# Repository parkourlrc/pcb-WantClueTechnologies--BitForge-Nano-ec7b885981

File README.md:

# 🪙 Open Source Bitcoin Miner PCB – CERN OHL 2 - S Licensed

This project presents a fully open-source Bitcoin mining hardware platform, designed for transparency, modularity, and extensibility. Built around the BM1370 ASICs and powered by an ESP32-S3 microcontroller, this board offers a compact yet powerful solution for enthusiasts and developers interested in cryptocurrency mining hardware.

Released under the **CERN OHL 2 S**, all design files, firmware, and documentation are freely available for use, modification, and redistribution.

---

## 📌 Key Features

- **Open Source Hardware & Firmware** – CERN-OHL-S licensed
- **Dual BM1370 ASICs** for parallel mining
- **ESP32-S3** as the central controller
- **Precision power monitoring** via INA260
- **Multi-stage voltage regulation** from 12 V down to 0.8 V
- **UART communication** with level shifting
- **Temperature monitoring & fan control** per ASIC
- **USB-C interface** for firmware upload and updates
- **Status LEDs** for visual feedback
- **Modular I2C architecture** with multiplexer support

---

## 🔧 Technical Overview

### Power Architecture

The board is powered via a **12 V barrel jack**, with a recommended power supply of **at least 70 W** to ensure stable operation under full load. Power distribution is carefully managed through multiple buck converters:

- **TPS546A24 Buck Converter**: Converts 12 V to **1.2 V**, configurable via **SMBus/I2C**
- **12 V → 5 V Buck Converter**
- **5 V → 3.3 V Buck Converter**
- From 3.3 V, two reference voltages (**1.2 V and 0.8 V**) are derived for the ASICs

A **Texas Instruments INA260** is used to monitor the total current and voltage, providing accurate power consumption data for the entire board and its peripherals.

---

### ASICs & Communication

The core mining functionality is handled by **two BM1370 ASICs**, connected in parallel and powered by the regulated 1.2 V supply. These chips communicate via **UART**, with signal levels adjusted using a **SN74AVC level shifter** to ensure compatibility between the ESP32-S3 and the ASICs.

Each ASIC requires two reference voltages (1.2 V and 0.8 V), which are derived from the 3.3 V rail using dedicated regulators.

---

### Thermal Management & Fan Control

Each BM1370 ASIC includes an internal die temperature sensor, which is monitored by an **EMC2101** temperature controller. These controllers also support **PWM fan control**, allowing each ASIC to drive a dedicated **12 V cooling fan**.

Since the EMC2101 has a fixed I2C address, a **PCA9544 I2C multiplexer** is used to switch between the two devices, enabling independent monitoring and control.

---

### Control & Interfaces

At the heart of the board is an **ESP32-S3**, which runs the firmware responsible for:

- ASIC initialization and control
- Power and temperature monitoring
- Fan speed regulation
- Communication via UART and I2C
- Status indication via **two onboard LEDs**

A **USB-C port** is provided for firmware flashing and future updates, making development and deployment straightforward.

---

## 🛠️ Open Source & Licensing

This project is proudly released under the **CERN Open Hardware Licence Version 2 - Strongly Reciprocal (CERN-OHL-S)**. This means:

- You are free to use, study, modify, and distribute the hardware designs
- Any derivative work must also be released under CERN-OHL-S
- If you manufacture or distribute products based on this design, you must provide recipients with access to the complete source files
- Contributions and improvements are welcome!

The CERN-OHL-S is specifically designed for open-source hardware, ensuring that designs remain open and accessible. We believe in open collaboration and transparency, and by releasing this project under CERN-OHL-S, we aim to foster innovation in the hardware mining community and provide a solid foundation for further development.

For the full license text, see the [LICENSE](LICENSE) file.

---

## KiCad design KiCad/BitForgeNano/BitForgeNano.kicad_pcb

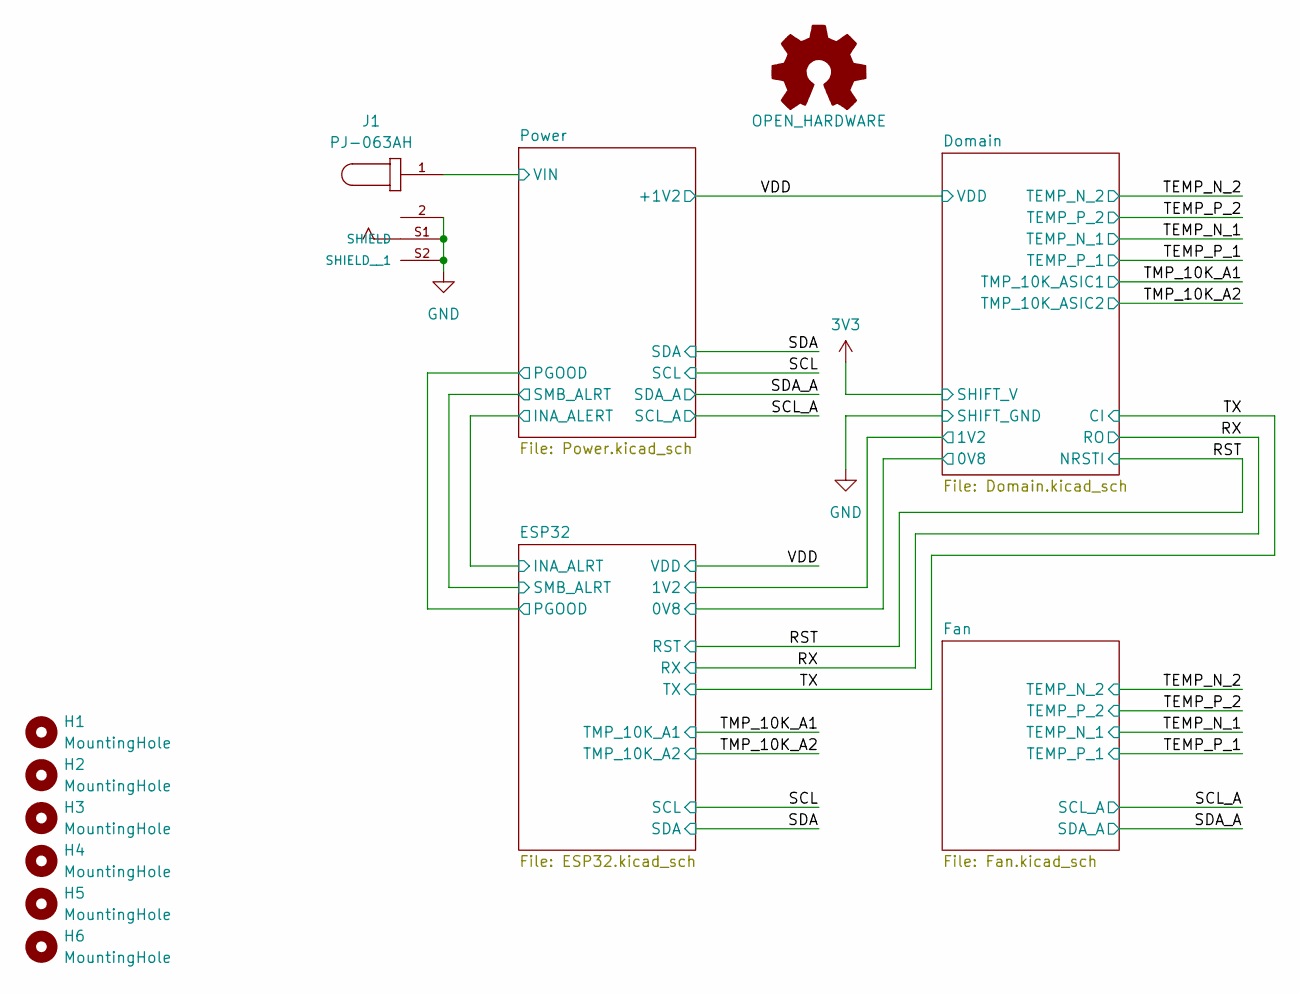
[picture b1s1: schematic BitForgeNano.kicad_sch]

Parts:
H1, H2, H3, H4, H5, H6: MountingHole; MountingHole_3.2mm_M3_ISO14580
J1: PJ-063AH; BarrelJack_CUI_PJ-063AH_Horizontal; PARTREV 1.02
LOGO1: OPEN_HARDWARE; OSHW-Logo_5.7x6mm_SilkScreen

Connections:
/Power/VIN: J1.1; also elsewhere on the board
GND: J1.2, J1.S1 (SHIELD), J1.S2 (SHIELD__1); also elsewhere on the board

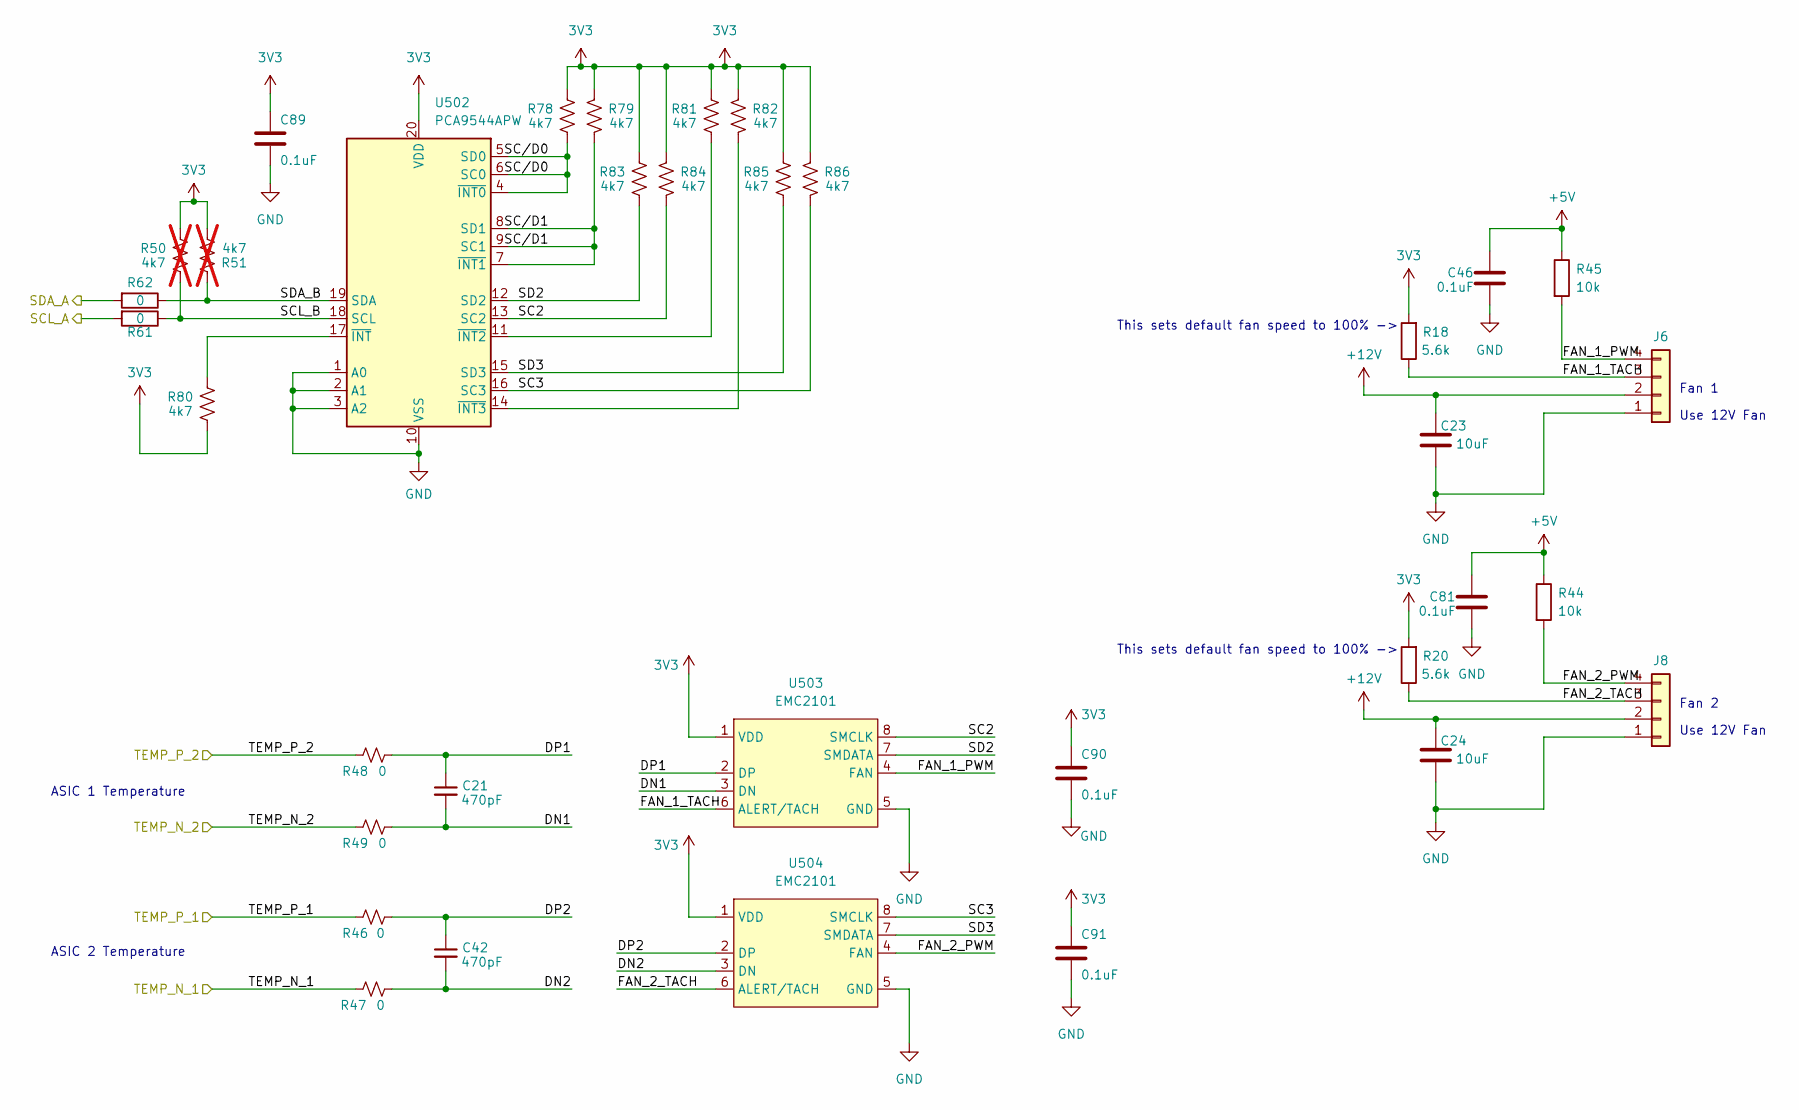
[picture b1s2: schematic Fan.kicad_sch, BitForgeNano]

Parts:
C21, C42: 470pF; C_0402_1005Metric; PARTNO GRM1555C1H471JA01D
C23, C24: 10uF; C_0603_1608Metric
C46, C81: 0.1uF; C_0402_1005Metric; PARTNO KGM05AR71C104KH
C89, C90, C91: 0.1uF; C_0402_1005Metric
J6, J8: Conn_01x04; 470531000; PARTNO 0470531000
R18, R20: 5.6k; R_0402_1005Metric
R44, R45: 10k; R_0402_1005Metric
R46, R47, R48, R49, R61, R62: 0; R_0402_1005Metric; PARTNO RC0402JR-070RL
R50, R51: 4k7; R_0805_2012Metric; not fitted
R78, R79, R80, R81, R82, R83, R84, R85, R86: 4k7; R_0402_1005Metric
U502: PCA9544APW; TSSOP-20_4.4x6.5mm_P0.65mm
U503, U504: EMC2101; TSSOP-8_3x3mm_P0.65mm; PARTNO EMC2101-R-ACZL-TR

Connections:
3V3: C89.1, C90.1, C91.1, R18.2, R20.2, R50.2, R51.1, R78.2, R79.2, R80.1, R81.2, R82.2, R83.2, R84.2, R85.2, R86.2, U502.20 (VDD), U503.1 (VDD), U504.1 (VDD); also elsewhere on the board
+5V: C46.1, C81.1, R44.1, R45.1; also elsewhere on the board
+12V: C23.1, C24.1, J6.2, J8.2; also elsewhere on the board
/Fan/DN1: C21.2, R49.1, U503.3 (DN)
/Fan/DN2: C42.2, R47.1, U504.3 (DN)
/Fan/DP1: C21.1, R48.1, U503.2 (DP)
/Fan/DP2: C42.1, R46.1, U504.2 (DP)
/Fan/FAN_1_PWM: J6.4, R45.2, U503.4 (FAN)
/Fan/FAN_1_TACH: J6.3, R18.1, U503.6 (ALERT/TACH)
/Fan/FAN_2_PWM: J8.4, R44.2, U504.4 (FAN)
/Fan/FAN_2_TACH: J8.3, R20.1, U504.6 (ALERT/TACH)
/Fan/SC2: R84.1, U502.13 (SC2), U503.8 (SMCLK)
/Fan/SC3: R86.1, U502.16 (SC3), U504.8 (SMCLK)
/Fan/SCL_B: R50.1, R61.1, U502.18 (SCL)
/Fan/SC/D0: R78.1, U502.4 (~INT0), U502.5 (SD0), U502.6 (SC0)
/Fan/SC/D1: R79.1, U502.7 (~INT1), U502.8 (SD1), U502.9 (SC1)
/Fan/SD2: R83.1, U502.12 (SD2), U503.7 (SMDATA)
/Fan/SD3: R85.1, U502.15 (SD3), U504.7 (SMDATA)
/Fan/SDA_B: R51.2, R62.1, U502.19 (SDA)
/SCL_A: R61.2; also elsewhere on the board
/SDA_A: R62.2; also elsewhere on the board
/TEMP_N_1: R47.2; also elsewhere on the board
/TEMP_N_2: R49.2; also elsewhere on the board
/TEMP_P_1: R46.2; also elsewhere on the board
/TEMP_P_2: R48.2; also elsewhere on the board
GND: C23.2, C24.2, C46.2, C81.2, C89.2, C90.2, C91.2, J6.1, J8.1, U502.1 (A0), U502.2 (A1), U502.3 (A2), U502.10 (VSS), U503.5 (GND), U504.5 (GND); also elsewhere on the board
unnamed: R81.1, U502.11 (~INT2)
unnamed: R82.1, U502.14 (~INT3)
unnamed: R80.2, U502.17 (~INT)

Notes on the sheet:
Fan 1
This sets default fan speed to 100% ->
ASIC 2 Temperature
Use 12V Fan
Fan 2
ASIC 1 Temperature

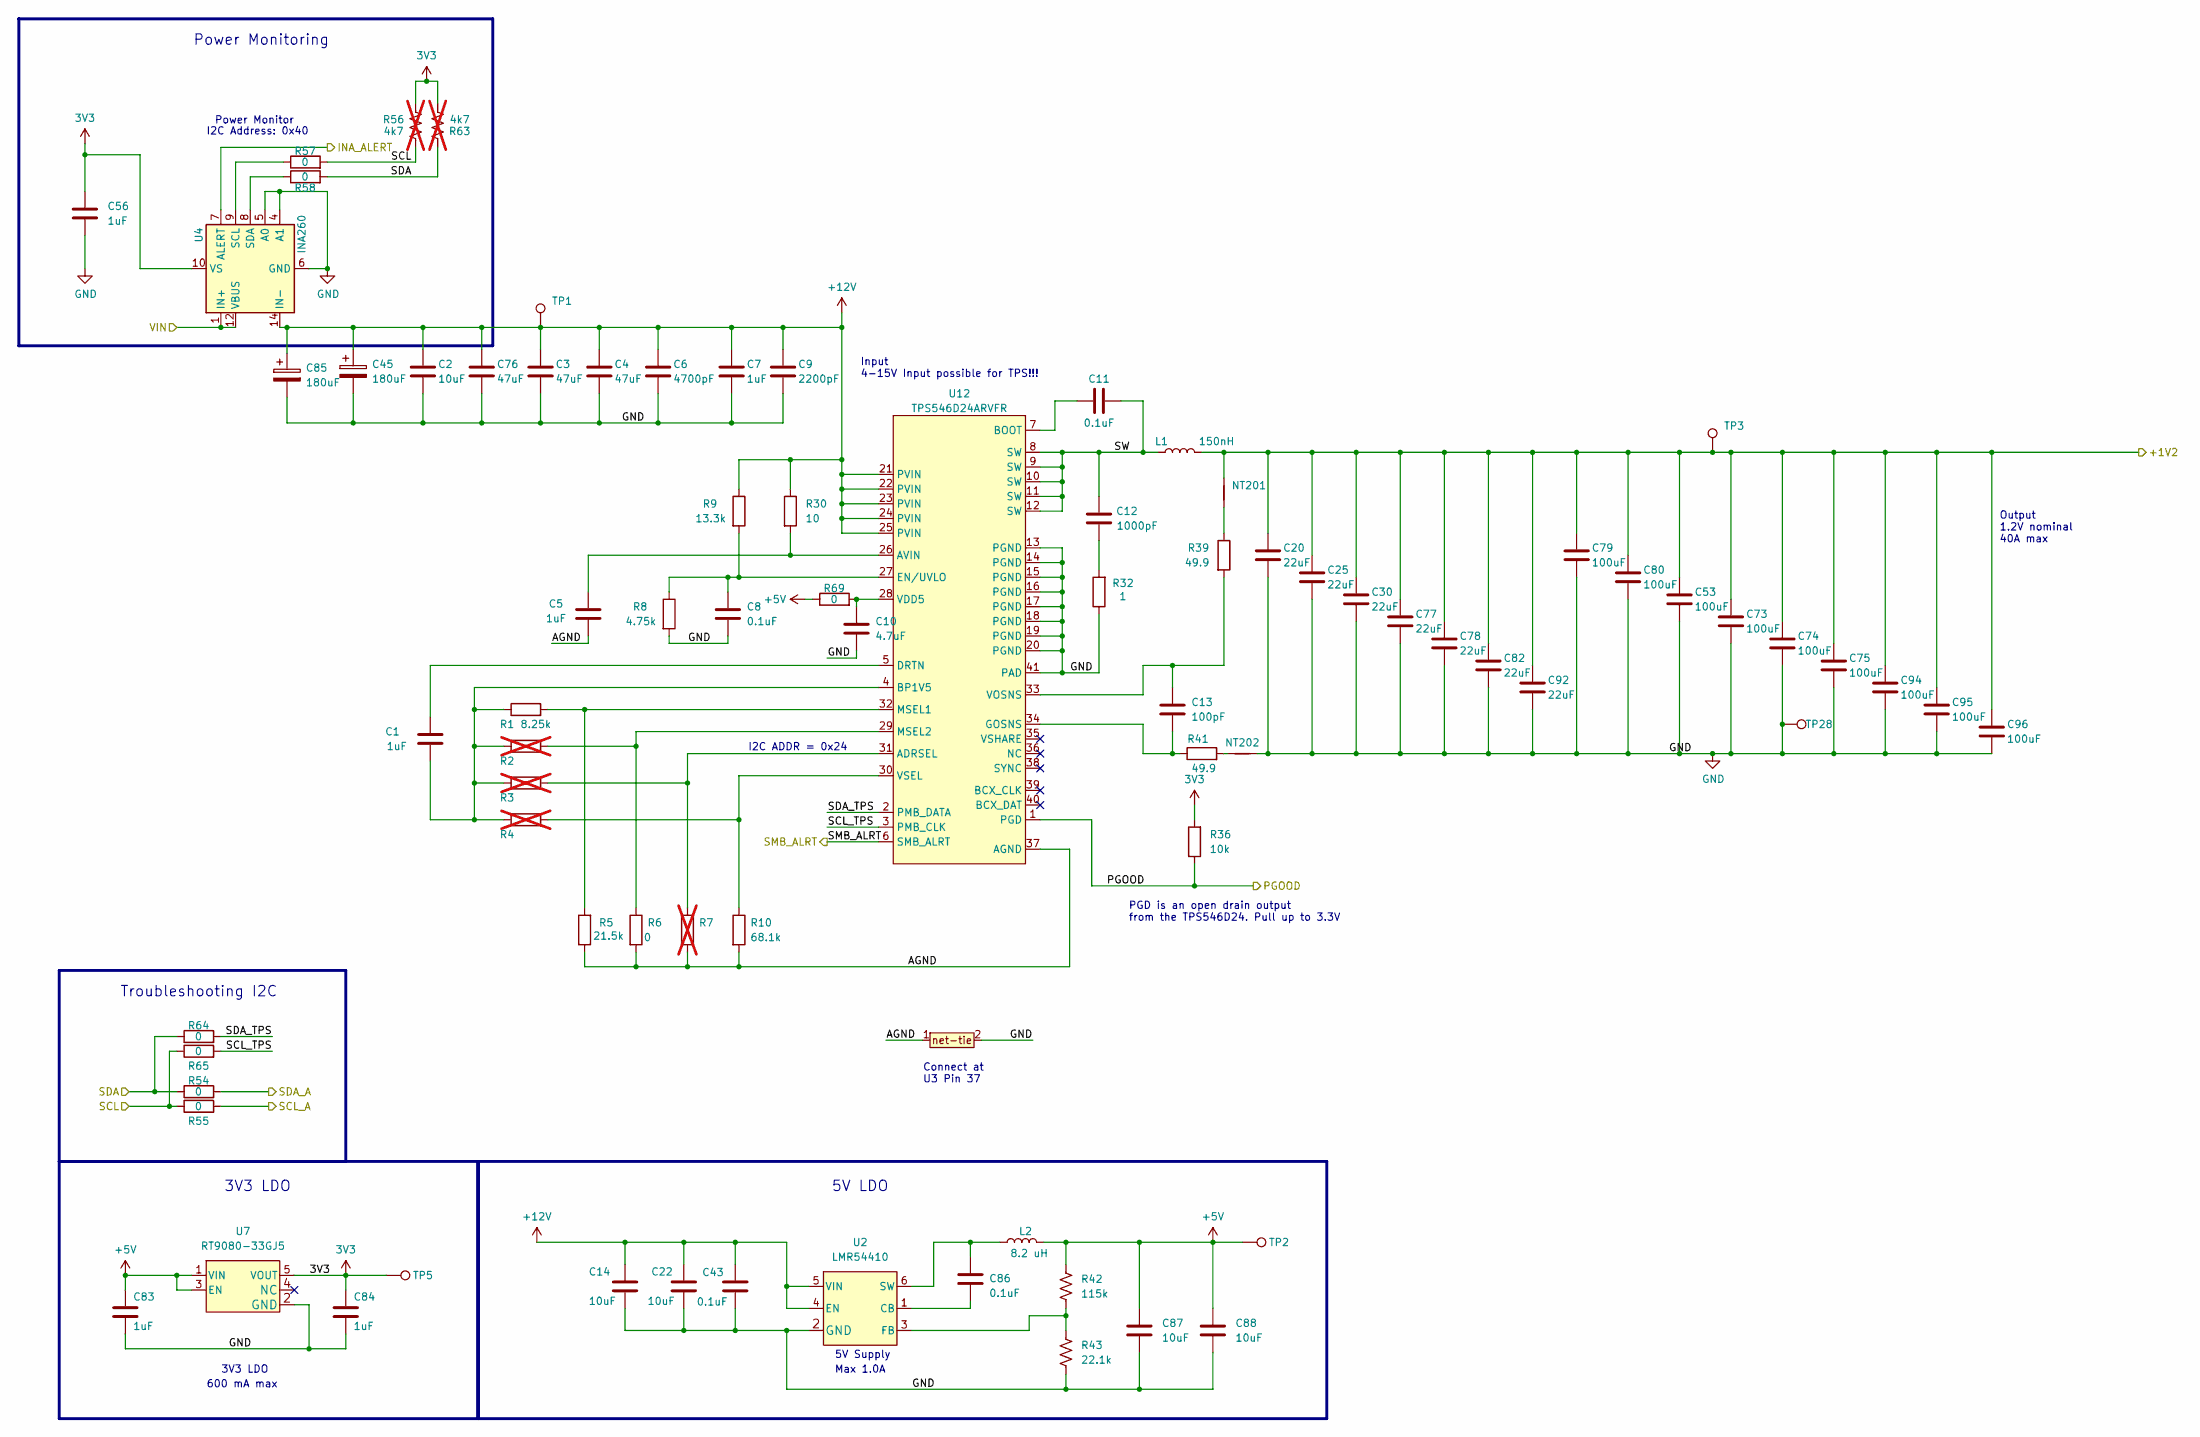
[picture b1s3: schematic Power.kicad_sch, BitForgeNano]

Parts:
C1, C5, C7, C56, C83, C84: 1uF; C_0402_1005Metric; PARTNO EMK105BJ105MV-F
C2: 10uF; C_0805_2012Metric; PARTNO CL21A106KOQNNNE
C3, C4, C76: 47uF; C_1210_3225Metric; PARTNO CL32A476KOJNNNE
C6: 4700pF; C_0402_1005Metric; PARTNO GRM155R71E472KA01D
C8, C11: 0.1uF; C_0402_1005Metric; PARTNO CL05A104KO5NNNC
C9: 2200pF; C_0402_1005Metric; PARTNO GRM155R61H222KA01D
C10: 4.7uF; C_0402_1005Metric; PARTNO GRM155R61A475MEAAD
C12: 1000pF; C_0805_2012Metric; PARTNO CC0805KRX7R9BB102
C13: 100pF; C_0402_1005Metric; PARTNO 885012005013
C14, C22, C87, C88: 10uF; C_0805_2012Metric; PARTNO GRM21BR61H106ME43L
C20, C25, C30, C77, C78, C82, C92: 22uF; C_0805_2012Metric; PARTNO GRM21BR61A226ME44L
C43: 0.1uF; C_0603_1608Metric; PARTNO KGM15BR71H104KT
C45, C85: 180uF; CP_Elec_6.3x5.9; PARTNO 16SVPF180M
C53, C73, C74, C75, C79, C80, C94, C95, C96: 100uF; C_1206_3216Metric; PARTNO CL31A107MQHNNNE
C86: 0.1uF; C_0402_1005Metric; PARTNO KGM05AR71C104KH
L1: 150nH; FP1007R3-R15-R; PARTNO FP1007R3-R15-R
L2: 8.2 uH; Inductor-74438357082; PARTNO 78438357082
NT201, NT202: NetTie_2; NetTie-2_SMD_Pad0.5mm
R1: 8.25k; R_0402_1005Metric; PARTNO CRCW040214K7FKED
R2, R3, R4, R7: R_0402_1005Metric; not fitted
R5: 21.5k; R_0402_1005Metric; PARTNO CRCW040221K5FKED
R6, R54, R55, R57, R58, R64, R65, R69: 0; R_0402_1005Metric; PARTNO RC0402JR-070RL
R8: 4.75k; R_0402_1005Metric; PARTNO CRCW04024K75FKED
R9: 13.3k; R_0402_1005Metric; PARTNO CRCW040213K3FKED
R10: 68.1k; R_0402_1005Metric; PARTNO RC0402FR-0768K1L
R30: 10; R_0402_1005Metric; PARTNO RC0402FR-0710RL
R32: 1; R_1206_3216Metric; PARTNO CSR1206FT1R00
R36: 10k; R_0402_1005Metric; PARTNO RC0402JR-0710KL
R39, R41: 49.9; R_0402_1005Metric; PARTNO RC0402FR-0749R9L
R42: 115k; R_0402_1005Metric; PARTNO RC0402FR-07115KL
R43: 22.1k; R_0402_1005Metric; PARTNO RC0402FR-0722K1L
R56, R63: 4k7; R_0402_1005Metric; not fitted
T1: net-tie; NetTie-2_SMD_Pad0.5mm
TP1, TP2, TP3, TP5: TestPoint; TestPoint_Pad_D1.0mm
TP28: TestPoint; TestPoint_Pad_D1.5mm
U2: LMR54410; SOT-23-6; PARTNO LMR54410FDBVR
U4: INA260; TSSOP-16_4.4x5mm_P0.65mm; PARTNO INA260AIPWR
U7: RT9080-33GJ5; PARTNO RT9080-33GJ5
U12: TPS546D24ARVFR; LQFN40-CLIP; PARTNO TPS546D24ARVFR

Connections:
3V3: C56.1, C84.1, R36.2, R56.2, R63.1, TP5.1, U4.10 (VS), U7.5 (VOUT); also elsewhere on the board
+5V: C83.1, C87.1, C88.1, L2.2, R42.1, R69.1, TP2.1, U7.1 (VIN), U7.3 (EN); also elsewhere on the board
+12V: C2.1, C3.1, C4.1, C6.1, C7.1, C9.1, C14.1, C22.1, C43.2, C45.1, C76.1, C85.1, R9.1, R30.1, TP1.1, U2.4 (EN), U2.5 (VIN), U4.14 (IN-), U4.15 (IN-), U4.16 (IN-), U12.21 (PVIN), U12.22 (PVIN), U12.23 (PVIN), U12.24 (PVIN), U12.25 (PVIN); also elsewhere on the board
/ESP32/INA_ALRT: U4.7 (ALERT); also elsewhere on the board
/Power/AGND: C5.1, R5.1, R6.2, R7.2, R10.2, T1.1, U12.37 (AGND)
/Power/PGOOD: R36.1, U12.1 (PGD); also elsewhere on the board
/Power/SCL_TPS: R65.2, U12.3 (PMB_CLK)
/Power/SDA_TPS: R64.2, U12.2 (PMB_DATA)
/Power/SMB_ALRT: U12.6 (SMB_ALRT); also elsewhere on the board
/Power/SW: C11.2, C12.2, L1.1, U12.8 (SW), U12.9 (SW), U12.10 (SW), U12.11 (SW), U12.12 (SW)
/Power/VIN: U4.1 (IN+), U4.2 (IN+), U4.3 (IN+), U4.12 (VBUS); also elsewhere on the board
/SCL: R55.1, R56.1, R57.2, R65.1; also elsewhere on the board
/SCL_A: R55.2; also elsewhere on the board
/SDA: R54.1, R58.2, R63.2, R64.1; also elsewhere on the board
/SDA_A: R54.2; also elsewhere on the board
/VDD: C20.1, C25.1, C30.1, C53.1, C73.1, C74.1, C75.1, C77.1, C78.1, C79.1, C80.1, C82.1, C92.1, C94.1, C95.1, C96.1, L1.2, NT201.2, TP3.1; also elsewhere on the board
GND: C2.2, C3.2, C4.2, C6.2, C7.2, C8.2, C9.2, C10.2, C14.2, C20.2, C22.2, C25.2, C30.2, C43.1, C45.2, C53.2, C56.2, C73.2, C74.2, C75.2, C76.2, C77.2, C78.2, C79.2, C80.2, C82.2, C83.2, C84.2, C85.2, C87.2, C88.2, C92.2, C94.2, C95.2, C96.2, NT202.2, R8.2, R32.1, R43.2, T1.2, TP28.1, U2.2 (GND), U4.4 (A1), U4.5 (A0), U4.6 (GND), U4.11 (GND), U7.2 (GND), U12.13 (PGND), U12.14 (PGND), U12.15 (PGND), U12.16 (PGND), U12.17 (PGND), U12.18 (PGND), U12.19 (PGND), U12.20 (PGND), U12.41 (PAD); also elsewhere on the board
unnamed: C12.1, R32.2
unnamed: NT201.1, R39.1
unnamed: NT202.1, R41.2
unnamed: C86.2, U2.1 (CB)
unnamed: R42.2, R43.1, U2.3 (FB)
unnamed: C86.1, L2.1, U2.6 (SW)
unnamed: R57.1, U4.9 (SCL)
unnamed: R58.1, U4.8 (SDA)
unnamed: R3.2, R7.1, U12.31 (ADRSEL)
unnamed: C5.2, R30.2, U12.26 (AVIN)
unnamed: C11.1, U12.7 (BOOT)
unnamed: C1.2, R1.1, R2.1, R3.1, R4.1, U12.4 (BP1V5)
unnamed: C1.1, U12.5 (DRTN)
unnamed: C8.1, R8.1, R9.2, U12.27 (EN/UVLO)
unnamed: C13.2, R41.1, U12.34 (GOSNS)
unnamed: R1.2, R5.2, U12.32 (MSEL1)
unnamed: R2.2, R6.1, U12.29 (MSEL2)
unnamed: C10.1, R69.2, U12.28 (VDD5)
unnamed: C13.1, R39.2, U12.33 (VOSNS)
unnamed: R4.2, R10.1, U12.30 (VSEL)

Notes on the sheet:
600 mA max
Power Monitor
PGD is an open drain output from the TPS546D24. Pull up to 3.3V
3V3 LDO
5V Supply
Max 1.0A
Output 1.2V nominal 40A max
I2C ADDR = 0x24
Power Monitoring
Connect at U3 Pin 37
I2C Address: 0x40
Troubleshooting I2C
5V LDO
Input 4-15V Input possible for TPS!!!

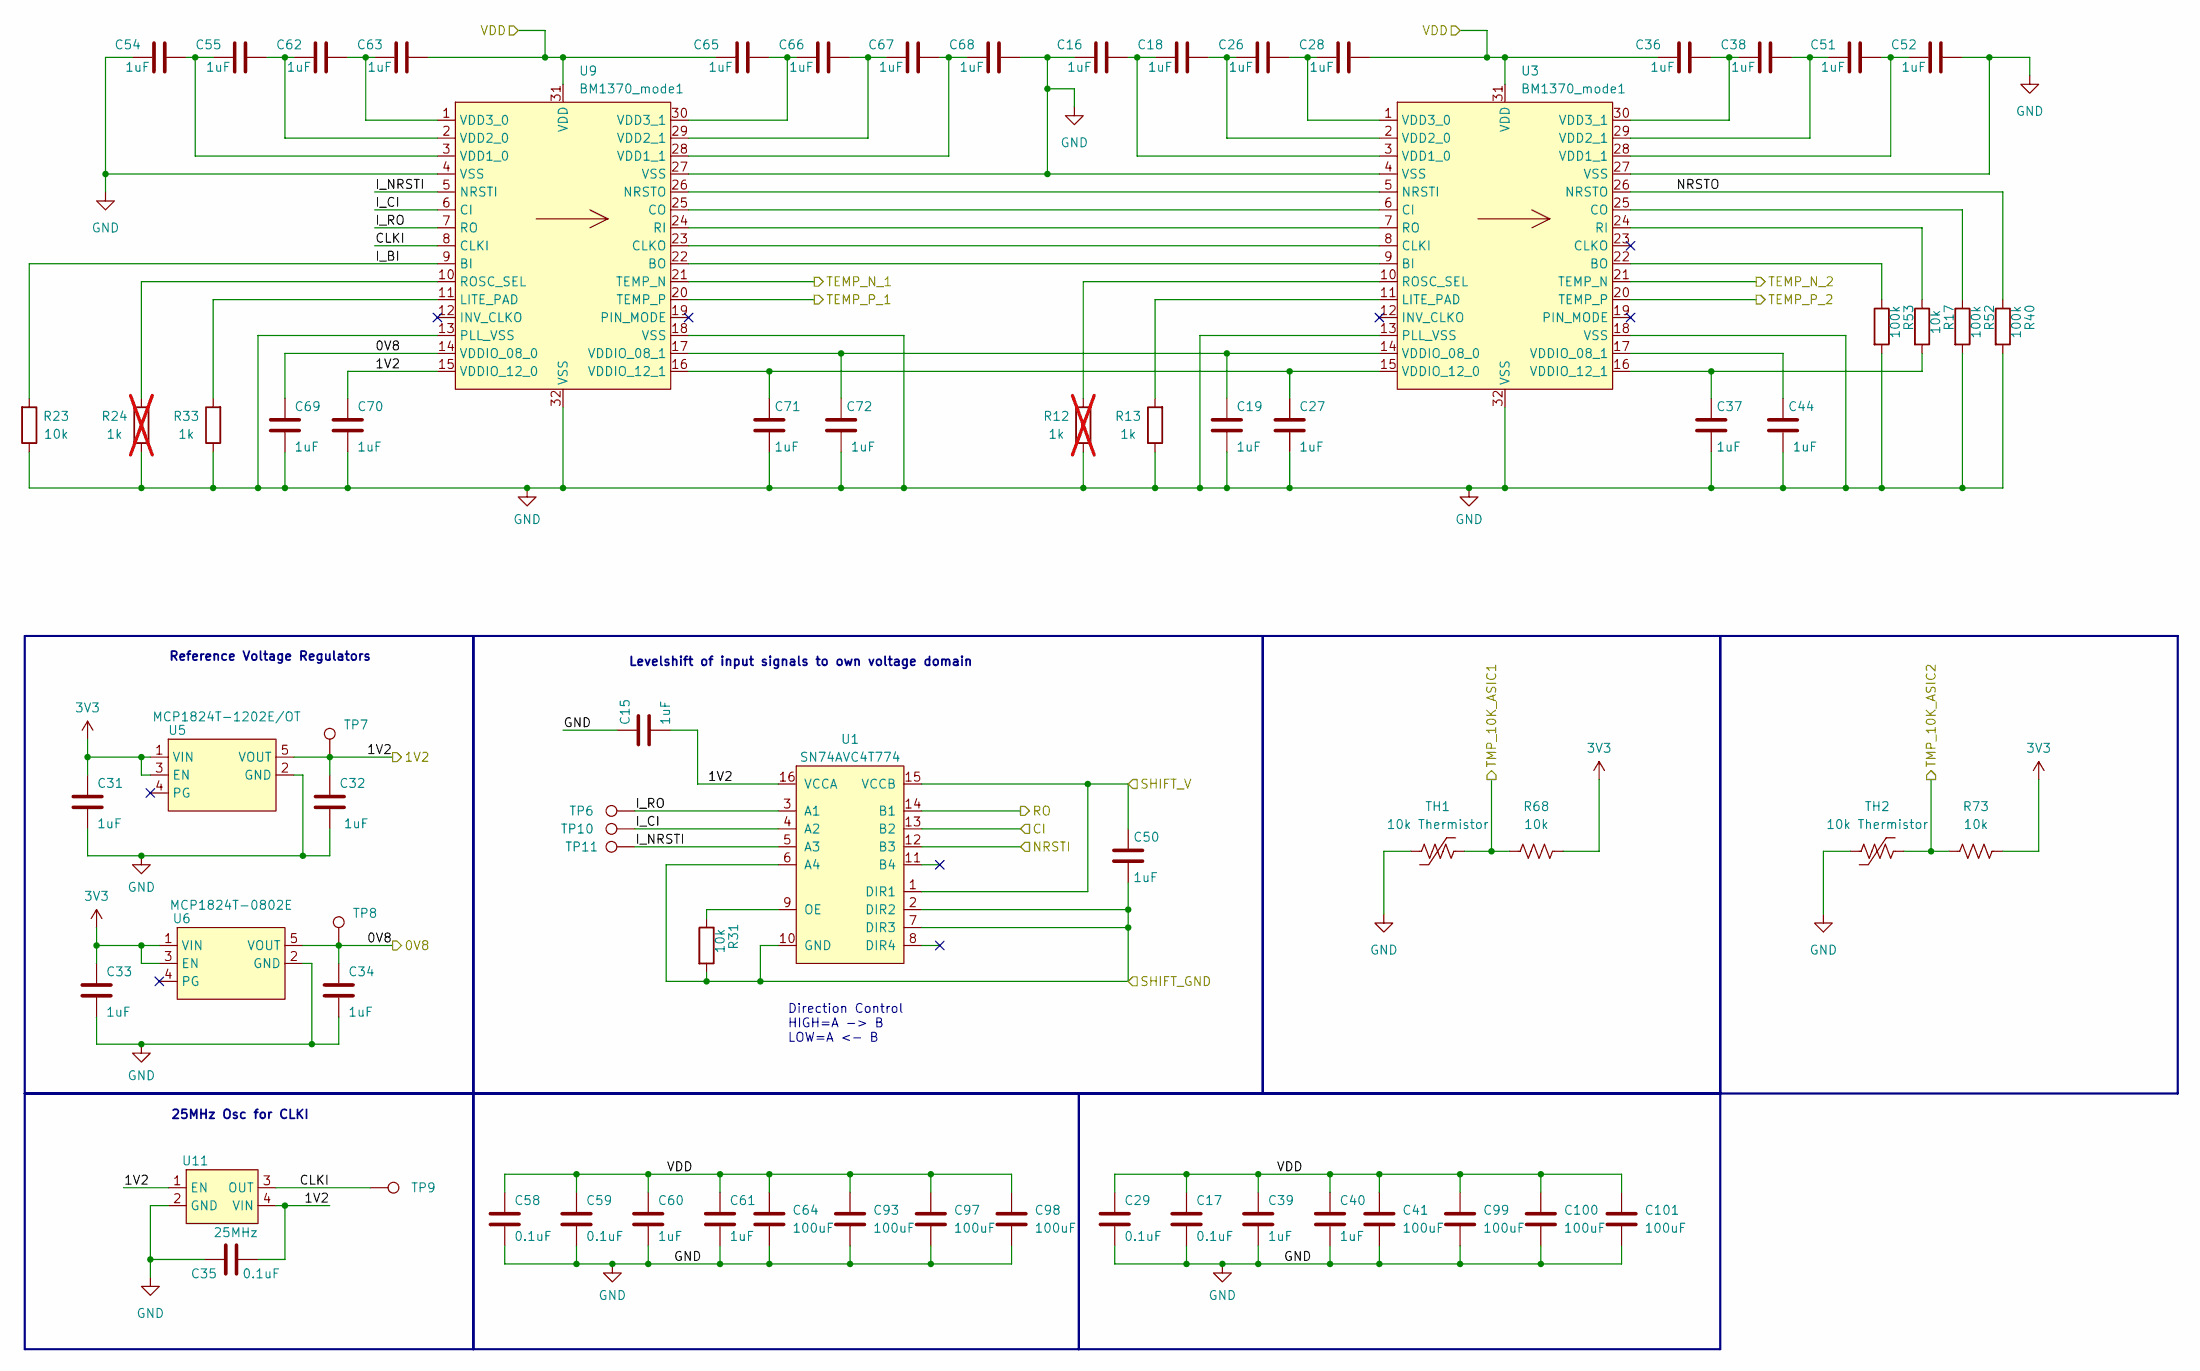
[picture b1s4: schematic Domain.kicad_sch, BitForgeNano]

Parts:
C15, C16, C18, C19, C26, C27, C28, C31, C32, C33, C34, C36, C37, C38, C39, C40, C44, C50, C51, C52, C54, C55, C60, C61, C62, C63, C65, C66, C67, C68, C69, C70, C71, C72: 1uF; C_0402_1005Metric; PARTNO EMK105BJ105MV-F
C17, C29, C35, C58, C59: 0.1uF; C_0805_2012Metric; PARTNO 0402X104K100CT
C41, C64: 100uF; C_1210_3225Metric
C93, C97, C98, C99, C100, C101: 100uF; C_1206_3216Metric
R12, R24: 1k; R_0201_0603Metric; PARTNO RC0402FR-071KL; not fitted
R13, R33: 1k; R_0402_1005Metric; PARTNO RC0402FR-071KL
R17, R31: 10k; R_0402_1005Metric
R23, R68, R73: 10k; R_0402_1005Metric; PARTNO RC0402JR-0710KL
R40, R52, R53: 100k; R_0402_1005Metric
TH1, TH2: 10k Thermistor; R_0402_1005Metric; PARTNO NTCG103JF103FT1
TP6, TP7, TP8, TP9, TP10, TP11: TestPoint; TestPoint_Pad_D1.0mm
U1: SN74AVC4T774; TSSOP-16_4.4x5mm_P0.65mm; PARTNO SN74AVC4T774PWR
U3, U9: BM1370_mode1; BM1370
U5: MCP1824T-1202E/OT; SOT-23-5; PARTNO MCP1824T-1202E/OT
U6: MCP1824T-0802E; SOT-23-5; PARTNO MCP1824T-0802E/OT
U11: 25MHz; O 25,0-JO32-B-1V3-1-T1-LF; PARTNO SX3M25.000E20F30THN; LCSC C5137262

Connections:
3V3: C31.1, C33.1, C50.1, R68.2, R73.2, U1.1 (DIR1), U1.15 (VCCB), U5.1 (VIN), U5.3 (EN), U6.1 (VIN), U6.3 (EN); also elsewhere on the board
/Domain/0V8: C34.1, C69.1, TP8.1, U6.5 (VOUT), U9.14 (VDDIO_08_0); also elsewhere on the board
/Domain/1V2: C15.2, C32.1, C35.2, C70.1, TP7.1, U1.16 (VCCA), U5.5 (VOUT), U9.15 (VDDIO_12_0), U11.1 (EN), U11.4 (VIN); also elsewhere on the board
/Domain/CLKI: TP9.1, U9.8 (CLKI), U11.3 (OUT)
/Domain/I_BI: R23.2, U9.9 (BI)
/Domain/I_CI: TP10.1, U1.4 (A2), U9.6 (CI)
/Domain/I_NRSTI: TP11.1, U1.5 (A3), U9.5 (NRSTI)
/Domain/I_RO: TP6.1, U1.3 (A1), U9.7 (RO)
/Domain/NRSTO: R40.1, U3.26 (NRSTO)
/RST: U1.12 (B3); also elsewhere on the board
/RX: U1.14 (B1); also elsewhere on the board
/TEMP_N_1: U9.21 (TEMP_N); also elsewhere on the board
/TEMP_N_2: U3.21 (TEMP_N); also elsewhere on the board
/TEMP_P_1: U9.20 (TEMP_P); also elsewhere on the board
/TEMP_P_2: U3.20 (TEMP_P); also elsewhere on the board
/TMP_10K_A1: R68.1, TH1.2; also elsewhere on the board
/TMP_10K_A2: R73.1, TH2.2; also elsewhere on the board
/TX: U1.13 (B2); also elsewhere on the board
/VDD: C17.1, C28.2, C29.1, C36.1, C39.1, C40.1, C41.1, C58.1, C59.1, C60.1, C61.1, C63.2, C64.1, C65.1, C93.1, C97.1, C98.1, C99.1, C100.1, C101.1, U3.31 (VDD), U9.31 (VDD); also elsewhere on the board
GND: C15.1, C16.1, C17.2, C19.2, C27.2, C29.2, C31.2, C32.2, C33.2, C34.2, C35.1, C37.2, C39.2, C40.2, C41.2, C44.2, C50.2, C52.2, C54.1, C58.2, C59.2, C60.2, C61.2, C64.2, C68.2, C69.2, C70.2, C71.2, C72.2, C93.2, C97.2, C98.2, C99.2, C100.2, C101.2, R12.1, R13.1, R23.1, R24.1, R31.2, R33.1, R40.2, R52.2, R53.2, TH1.1, TH2.1, U1.2 (DIR2), U1.6 (A4), U1.7 (DIR3), U1.10 (GND), U3.4 (VSS), U3.13 (PLL_VSS), U3.18 (VSS), U3.27 (VSS), U3.32 (VSS), U5.2 (GND), U6.2 (GND), U9.4 (VSS), U9.13 (PLL_VSS), U9.18 (VSS), U9.27 (VSS), U9.32 (VSS), U11.2 (GND); also elsewhere on the board
unnamed: R31.1, U1.9 (OE)
unnamed: U3.9 (BI), U9.22 (BO)
unnamed: R53.1, U3.22 (BO)
unnamed: U3.6 (CI), U9.25 (CO)
unnamed: U3.8 (CLKI), U9.23 (CLKO)
unnamed: R52.1, U3.25 (CO)
unnamed: R13.2, U3.11 (LITE_PAD)
unnamed: U3.5 (NRSTI), U9.26 (NRSTO)
unnamed: R17.1, U3.24 (RI)
unnamed: U3.7 (RO), U9.24 (RI)
unnamed: R12.2, U3.10 (ROSC_SEL)
unnamed: C16.2, C18.1, U3.3 (VDD1_0)
unnamed: C51.2, C52.1, U3.28 (VDD1_1)
unnamed: C18.2, C26.1, U3.2 (VDD2_0)
unnamed: C38.2, C51.1, U3.29 (VDD2_1)
unnamed: C26.2, C28.1, U3.1 (VDD3_0)
unnamed: C36.2, C38.1, U3.30 (VDD3_1)
unnamed: C19.1, C72.1, U3.14 (VDDIO_08_0), U9.17 (VDDIO_08_1)
unnamed: C44.1, U3.17 (VDDIO_08_1)
unnamed: C27.1, C71.1, U3.15 (VDDIO_12_0), U9.16 (VDDIO_12_1)
unnamed: C37.1, R17.2, U3.16 (VDDIO_12_1)
unnamed: R33.2, U9.11 (LITE_PAD)
unnamed: R24.2, U9.10 (ROSC_SEL)
unnamed: C54.2, C55.1, U9.3 (VDD1_0)
unnamed: C67.2, C68.1, U9.28 (VDD1_1)
unnamed: C55.2, C62.1, U9.2 (VDD2_0)
unnamed: C66.2, C67.1, U9.29 (VDD2_1)
unnamed: C62.2, C63.1, U9.1 (VDD3_0)
unnamed: C65.2, C66.1, U9.30 (VDD3_1)

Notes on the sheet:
25MHz Osc for CLKI
Direction Control HIGH=A -> B LOW=A <- B
Levelshift of input signals to own voltage domain
Reference Voltage Regulators

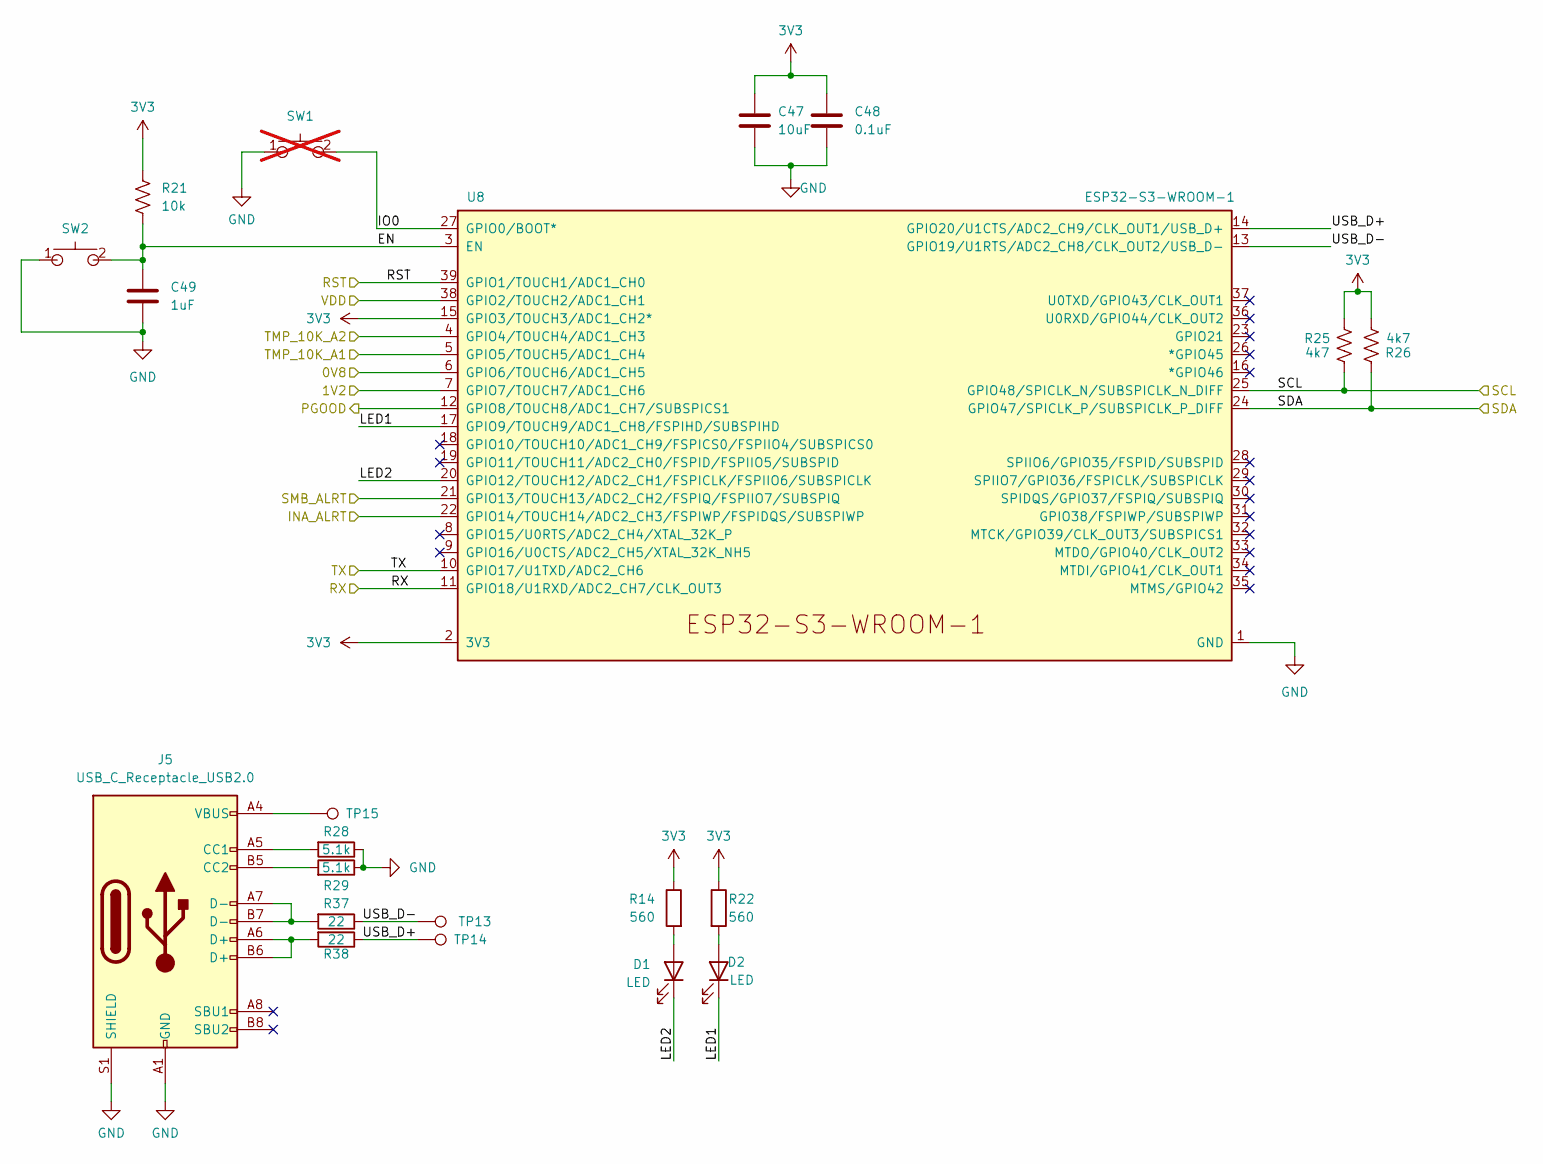
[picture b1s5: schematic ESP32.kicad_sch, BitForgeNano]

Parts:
C47: 10uF; C_0805_2012Metric; PARTNO CL21A106KOQNNNE
C48: 0.1uF; C_0805_2012Metric; PARTNO 0402X104K100CT
C49: 1uF; C_0805_2012Metric; PARTNO EMK105BJ105MV-F
D1, D2: LED; LED_0603_1608Metric
J5: USB_C_Receptacle_USB2.0; USB_C_Receptacle_GCT_USB4105-xx-A_16P_TopMnt_Horizontal
R14, R22: 560; R_0402_1005Metric
R21: 10k; R_0805_2012Metric; PARTNO RC0402JR-0710KL
R25, R26: 4k7; R_0402_1005Metric
R28, R29: 5.1k; R_0805_2012Metric
R37, R38: 22; R_0805_2012Metric
SW1: GT-TC029B-H025-L1N; SW_CS1213AGF260_CRS; PARTNO CS1213AGF260; not fitted
SW2: GT-TC029B-H025-L1N; SW_CS1213AGF260_CRS; PARTNO CS1213AGF260
TP13, TP14, TP15: TestPoint; TestPoint_Pad_D1.0mm
U8: ESP32-S3-WROOM-1; PARTNO ESP32-S3-WROOM-1-N16R8

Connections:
3V3: C47.1, C48.1, R14.1, R21.1, R22.1, R25.2, R26.1, U8.2 (3V3), U8.15 (GPIO3/TOUCH3/ADC1_CH2*); also elsewhere on the board
/Domain/0V8: U8.6 (GPIO6/TOUCH6/ADC1_CH5); also elsewhere on the board
/Domain/1V2: U8.7 (GPIO7/TOUCH7/ADC1_CH6); also elsewhere on the board
/ESP32/EN: C49.1, R21.2, SW2.2, U8.3 (EN)
/ESP32/INA_ALRT: U8.22 (GPIO14/TOUCH14/ADC2_CH3/FSPIWP/FSPIDQS/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); also elsewhere on the board
/ESP32/IO0: SW1.2, U8.27 (GPIO0/BOOT*)
/ESP32/LED1: D2.1 (K), U8.17 (GPIO9/TOUCH9/ADC1_CH8/FSPIHD/SUBSPIHD)
/ESP32/LED2: D1.1 (K), U8.20 (GPIO12/TOUCH12/ADC2_CH1/FSPICLK/FSPIIO6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)
/ESP32/USB_D+: R38.1, TP14.1, U8.14 (GPIO20/U1CTS/ADC2_CH9/CLK_OUT1/USB_D+)
/ESP32/USB_D-: R37.1, TP13.1, U8.13 (GPIO19/U1RTS/ADC2_CH8/CLK_OUT2/USB_D-)
/Power/PGOOD: U8.12 (GPIO8/TOUCH8/ADC1_CH7/SUBSPICS1); also elsewhere on the board
/Power/SMB_ALRT: U8.21 (GPIO13/TOUCH13/ADC2_CH2/FSPIQ/FSPIIO7/S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); also elsewhere on the board
/RST: U8.39 (GPIO1/TOUCH1/ADC1_CH0); also elsewhere on the board
/RX: U8.11 (GPIO18/U1RXD/ADC2_CH7/CLK_OUT3); also elsewhere on the board
/SCL: R25.1, U8.25 (GPIO48/SPICLK_N/SUBSPICLK_N_DIFF); also elsewhere on the board
/SDA: R26.2, U8.24 (GPIO47/SPICLK_P/SUBSPICLK_P_DIFF); also elsewhere on the board
/TMP_10K_A1: U8.5 (GPIO5/TOUCH5/ADC1_CH4); also elsewhere on the board
/TMP_10K_A2: U8.4 (GPIO4/TOUCH4/ADC1_CH3); also elsewhere on the board
/TX: U8.10 (GPIO17/U1TXD/ADC2_CH6); also elsewhere on the board
/VDD: U8.38 (GPIO2/TOUCH2/ADC1_CH1); also elsewhere on the board
GND: C47.2, C48.2, C49.2, J5.A1 (GND), J5.A12 (GND), J5.B1 (GND), J5.B12 (GND), J5.S1 (SHIELD), R28.1, R29.1, SW1.1, SW2.1, U8.1 (GND), U8.40 (GND), U8.41 (GND); also elsewhere on the board
unnamed: D1.2 (A), R14.2
unnamed: D2.2 (A), R22.2
unnamed: J5.A5 (CC1), R28.2
unnamed: J5.B5 (CC2), R29.2
unnamed: J5.A6 (D+), J5.B6 (D+), R38.2
unnamed: J5.A7 (D-), J5.B7 (D-), R37.2
unnamed: J5.A4 (VBUS), J5.A9 (VBUS), J5.B4 (VBUS), J5.B9 (VBUS), TP15.1

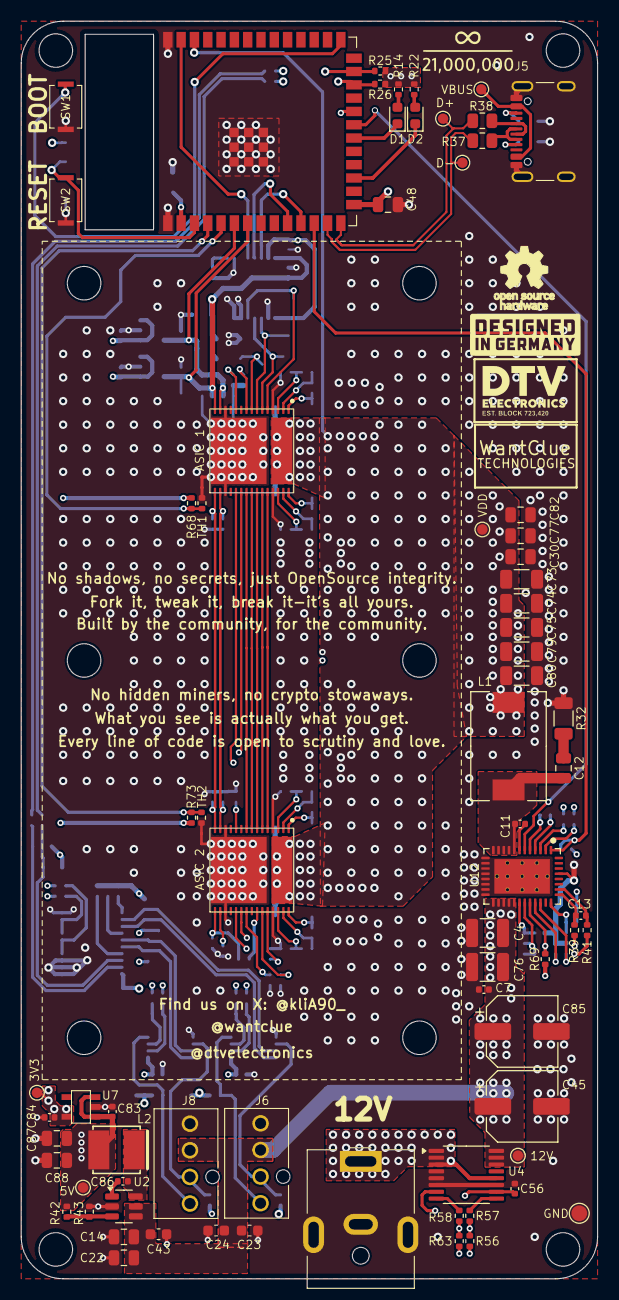
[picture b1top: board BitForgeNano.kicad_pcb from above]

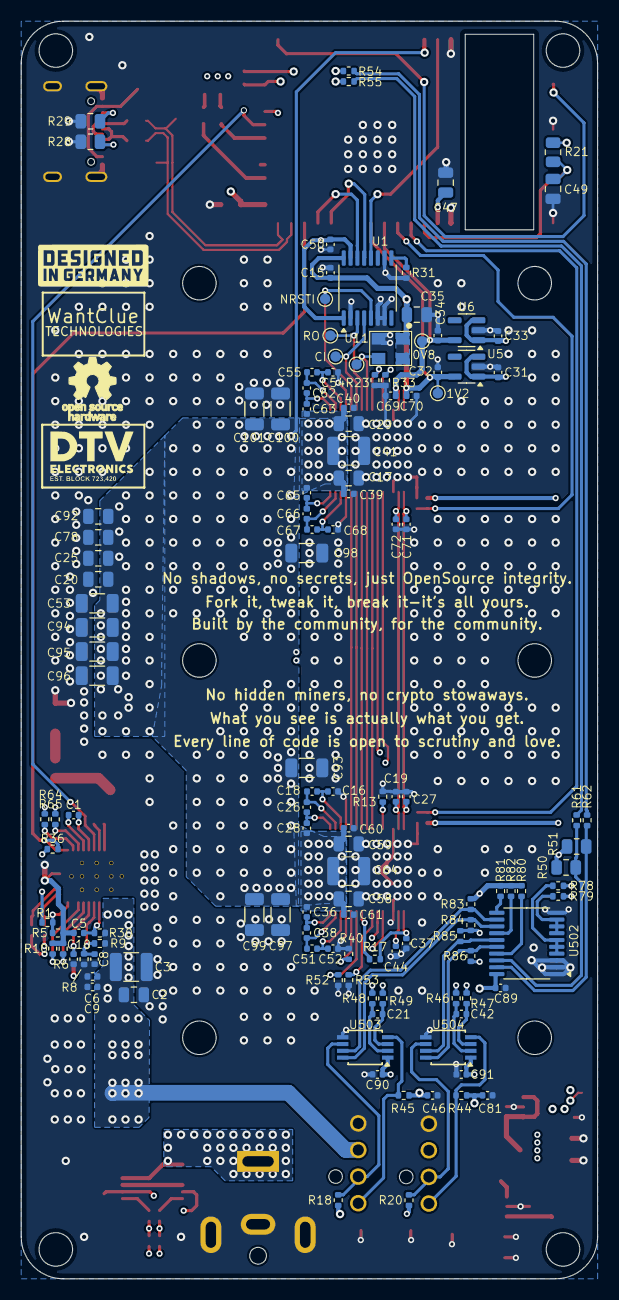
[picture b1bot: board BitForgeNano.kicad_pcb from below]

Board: 6 copper layers, 55.0 x 120.0 mm, 211 parts (130 on the bottom side), 110 nets.

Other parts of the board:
LOGO1#2: OPEN_HARDWARE; OSHW-Logo_5.7x6mm_SilkScreen

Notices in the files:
KiCad/BitForgeNano/BitForgeNano.kicad_sch:
Licensed under CERN-OHL-W version 2
